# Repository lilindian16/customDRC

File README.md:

# Custom DRC for the Bit10 DSP

## Reverse Engineering

### Bit10 DRC Schema

## CustomDRC

### Bare PCB

### Assembled Board

Boards can be programmed via TC2030 header or 2.54mm pin header (left unpopulated). Once programmed,
further updates can be handled via the OTA Update interface through the local webapp

### Board Bringup - Scope Captures

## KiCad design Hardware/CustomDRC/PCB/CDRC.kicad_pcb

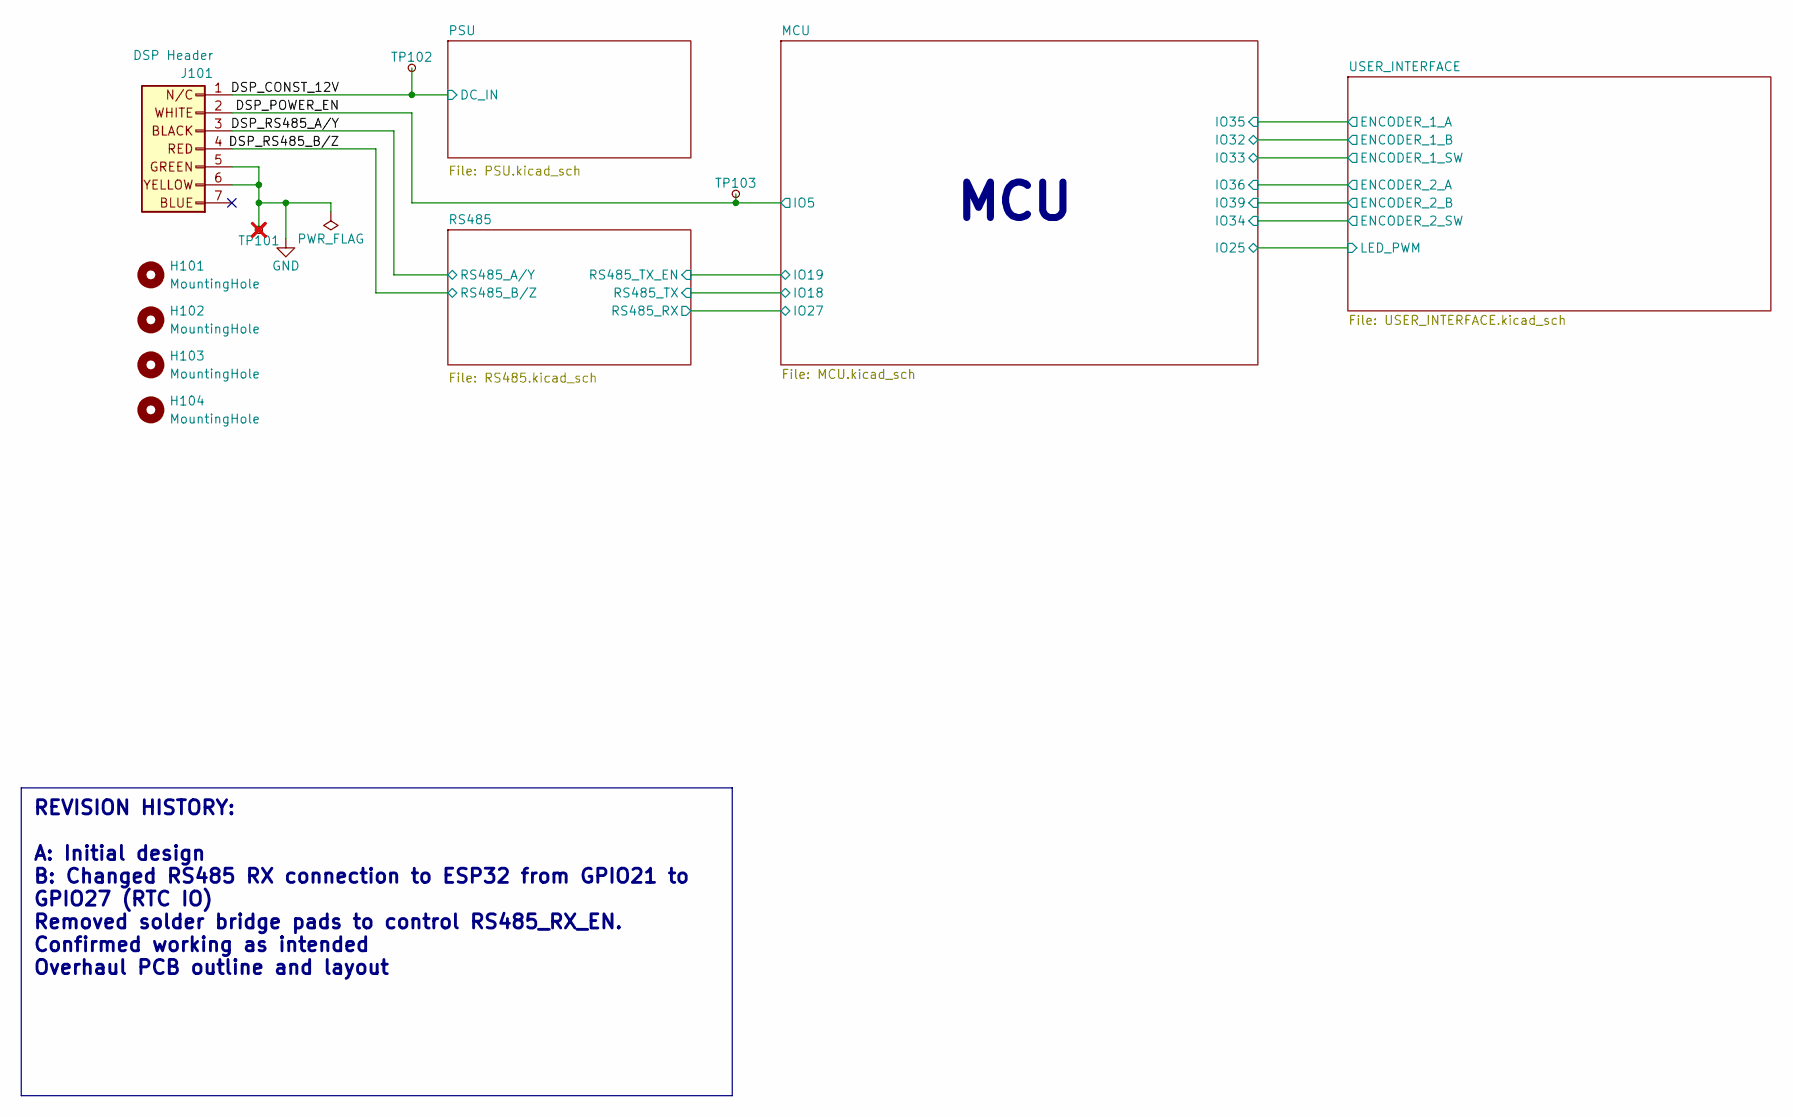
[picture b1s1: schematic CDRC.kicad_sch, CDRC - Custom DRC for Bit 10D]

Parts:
H101, H102, H103, H104: MountingHole; MountingHole_2.7mm_M2.5_ISO7380_Pad_TopBottom
J101: DSP Header; M208900705; MPN KH-2.54PH-1X30P-L13.5-WT; LCSC C20610239
TP101: TestPoint_Small; TestPoint_Keystone_5000-5004_Miniature; MPN RH-5001; LCSC C5199801; not fitted
TP102, TP103: TestPoint_Small; TestPoint_Pad_D1.5mm

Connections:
/DSP_CONST_12V: J101.1, TP102.1; also elsewhere on the board
/DSP_POWER_EN: J101.2, TP103.1; also elsewhere on the board
/DSP_RS485_A/Y: J101.3; also elsewhere on the board
/DSP_RS485_B/Z: J101.4; also elsewhere on the board
GND: J101.5, J101.6, TP101.1; also elsewhere on the board

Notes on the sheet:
REVISION HISTORY: A: Initial design B: Changed RS485 RX connection to ESP32 from GPIO21 to GPIO27 (RTC IO) Removed solder bridge pads to control RS485_RX_EN. Confirmed working as intended Overhaul PCB outline and layout
MCU

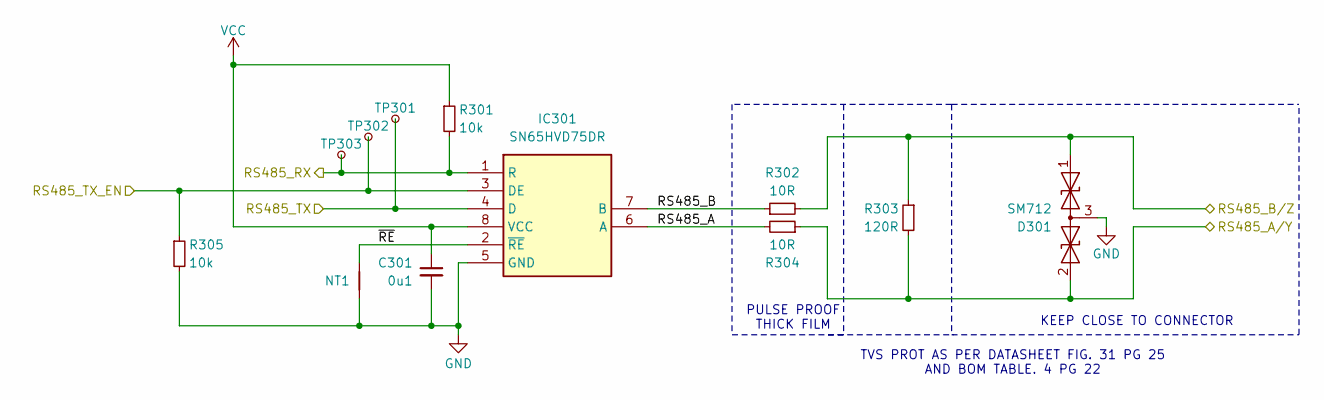
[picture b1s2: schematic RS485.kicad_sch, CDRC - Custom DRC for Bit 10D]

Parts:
C301: 0u1; C_0603_1608Metric_Pad1.08x0.95mm_HandSolder; MPN CC0603KRX7R9BB104; LCSC C14663
D301: SM712; SOT-23; MPN SM712; LCSC C5243888
IC301: SN65HVD75DR; SOIC-8_3.9x4.9mm_P1.27mm; Manufacturer_Part_Number SN65HVD75DR; Mouser Part Number 595-SN65HVD75DR
NT1: NetTie_2; NetTie-2_SMD_Pad0.5mm
R301, R305: 10k; R_0603_1608Metric_Pad0.98x0.95mm_HandSolder; MPN 0603WAF1002T5E; LCSC C25804
R302, R304: 10R; R_0603_1608Metric_Pad0.98x0.95mm_HandSolder; MPN CRCW060310R0FKTA; LCSC C2091419
R303: 120R; R_0603_1608Metric_Pad0.98x0.95mm_HandSolder; MPN 0603WAF1200T5E; LCSC C22787
TP301, TP302, TP303: TestPoint_Small; TestPoint_Pad_D1.5mm

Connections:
/DSP_RS485_A/Y: D301.2 (A2), R303.2, R304.1; also elsewhere on the board
/DSP_RS485_B/Z: D301.1 (A1), R302.2, R303.1; also elsewhere on the board
/MCU/IO18: IC301.4 (D), TP301.1; also elsewhere on the board
/MCU/IO19: IC301.3 (DE), R305.1, TP302.1; also elsewhere on the board
/MCU/IO27: IC301.1 (R), R301.2, TP303.1; also elsewhere on the board
/RS485/RS485_A: IC301.6 (A), R304.2
/RS485/RS485_B: IC301.7 (B), R302.1
/RS485/~RE: IC301.2 (~RE), NT1.2
GND: C301.2, D301.3 (common), IC301.5 (GND), NT1.1, R305.2; also elsewhere on the board
VCC: C301.1, IC301.8 (VCC), R301.1; also elsewhere on the board

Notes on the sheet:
KEEP CLOSE TO CONNECTOR
TVS PROT AS PER DATASHEET FIG. 31 PG 25 AND BOM TABLE. 4 PG 22
PULSE PROOF THICK FILM

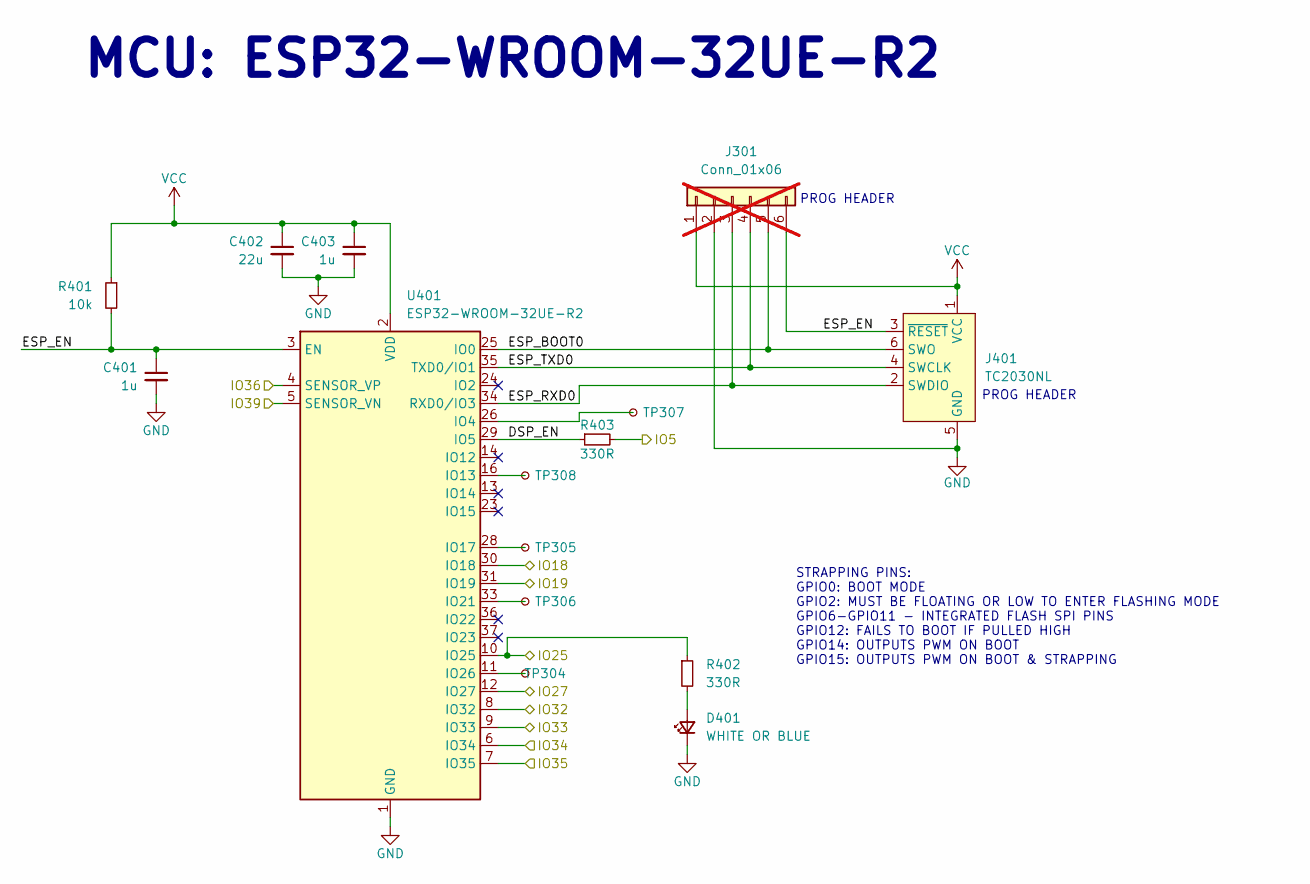
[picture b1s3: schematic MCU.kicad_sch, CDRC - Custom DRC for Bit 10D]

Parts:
C401, C403: 1u; C_0603_1608Metric_Pad1.08x0.95mm_HandSolder; MPN CL10A105KB8NNNC; LCSC C15849
C402: 22u; C_0805_2012Metric_Pad1.18x1.45mm_HandSolder; MPN CL21A226MAQNNNE; LCSC C45783
D401: WHITE OR BLUE; LED_0603_1608Metric_Pad1.05x0.95mm_HandSolder; MPN KT-0603W; LCSC C2290
J301: Conn_01x06; PinSocket_1x06_P2.54mm_Vertical; not fitted
J401: TC2030NL; Tag-Connect_TC2030-IDC-FP_2x03_P1.27mm_Vertical
R401: 10k; R_0603_1608Metric_Pad0.98x0.95mm_HandSolder; MPN 0603WAF1002T5E; LCSC C25804
R402, R403: 330R; R_0603_1608Metric_Pad0.98x0.95mm_HandSolder; MPN 0603WAF3300T5E; LCSC C23138
TP304, TP305, TP306, TP307, TP308: TestPoint_Small; TestPoint_Pad_D1.5mm
U401: ESP32-WROOM-32UE-R2; ESP32-WROOM-32UE; MPN ESP32-WROOM-32UE-N16; LCSC C701346

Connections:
/DSP_POWER_EN: R403.2; also elsewhere on the board
/MCU/DSP_EN: R403.1, U401.29 (IO5)
/MCU/ESP_BOOT0: J301.5, J401.6 (SWO), U401.25 (IO0)
/MCU/ESP_EN: C401.1, J301.6, J401.3 (~RESET), R401.2, U401.3 (EN)
/MCU/ESP_RXD0: J301.3, J401.2 (SWDIO), U401.34 (RXD0/IO3)
/MCU/ESP_TXD0: J301.4, J401.4 (SWCLK), U401.35 (TXD0/IO1)
/MCU/IO18: U401.30 (IO18); also elsewhere on the board
/MCU/IO19: U401.31 (IO19); also elsewhere on the board
/MCU/IO25: R402.1, U401.10 (IO25); also elsewhere on the board
/MCU/IO27: U401.12 (IO27); also elsewhere on the board
/MCU/IO32: U401.8 (IO32); also elsewhere on the board
/MCU/IO33: U401.9 (IO33); also elsewhere on the board
/MCU/IO34: U401.6 (IO34); also elsewhere on the board
/MCU/IO35: U401.7 (IO35); also elsewhere on the board
/MCU/IO36: U401.4 (SENSOR_VP); also elsewhere on the board
/MCU/IO39: U401.5 (SENSOR_VN); also elsewhere on the board
GND: C401.2, C402.2, C403.2, D401.1 (K), J301.2, J401.5 (GND), U401.1 (GND), U401.15 (GND), U401.38 (GND), U401.39 (GND); also elsewhere on the board
unnamed: D401.2 (A), R402.2
unnamed: TP307.1, U401.26 (IO4)
unnamed: TP308.1, U401.16 (IO13)
unnamed: TP305.1, U401.28 (IO17)
unnamed: TP306.1, U401.33 (IO21)
unnamed: TP304.1, U401.11 (IO26)
VCC: C402.1, C403.1, J301.1, J401.1 (VCC), R401.1, U401.2 (VDD); also elsewhere on the board

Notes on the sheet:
PROG HEADER
MCU: ESP32-WROOM-32UE-R2
STRAPPING PINS: GPIO0: BOOT MODE GPIO2: MUST BE FLOATING OR LOW TO ENTER FLASHING MODE GPIO6-GPIO11 - INTEGRATED FLASH SPI PINS GPIO12: FAILS TO BOOT IF PULLED HIGH GPIO14: OUTPUTS PWM ON BOOT GPIO15: OUTPUTS PWM ON BOOT & STRAPPING

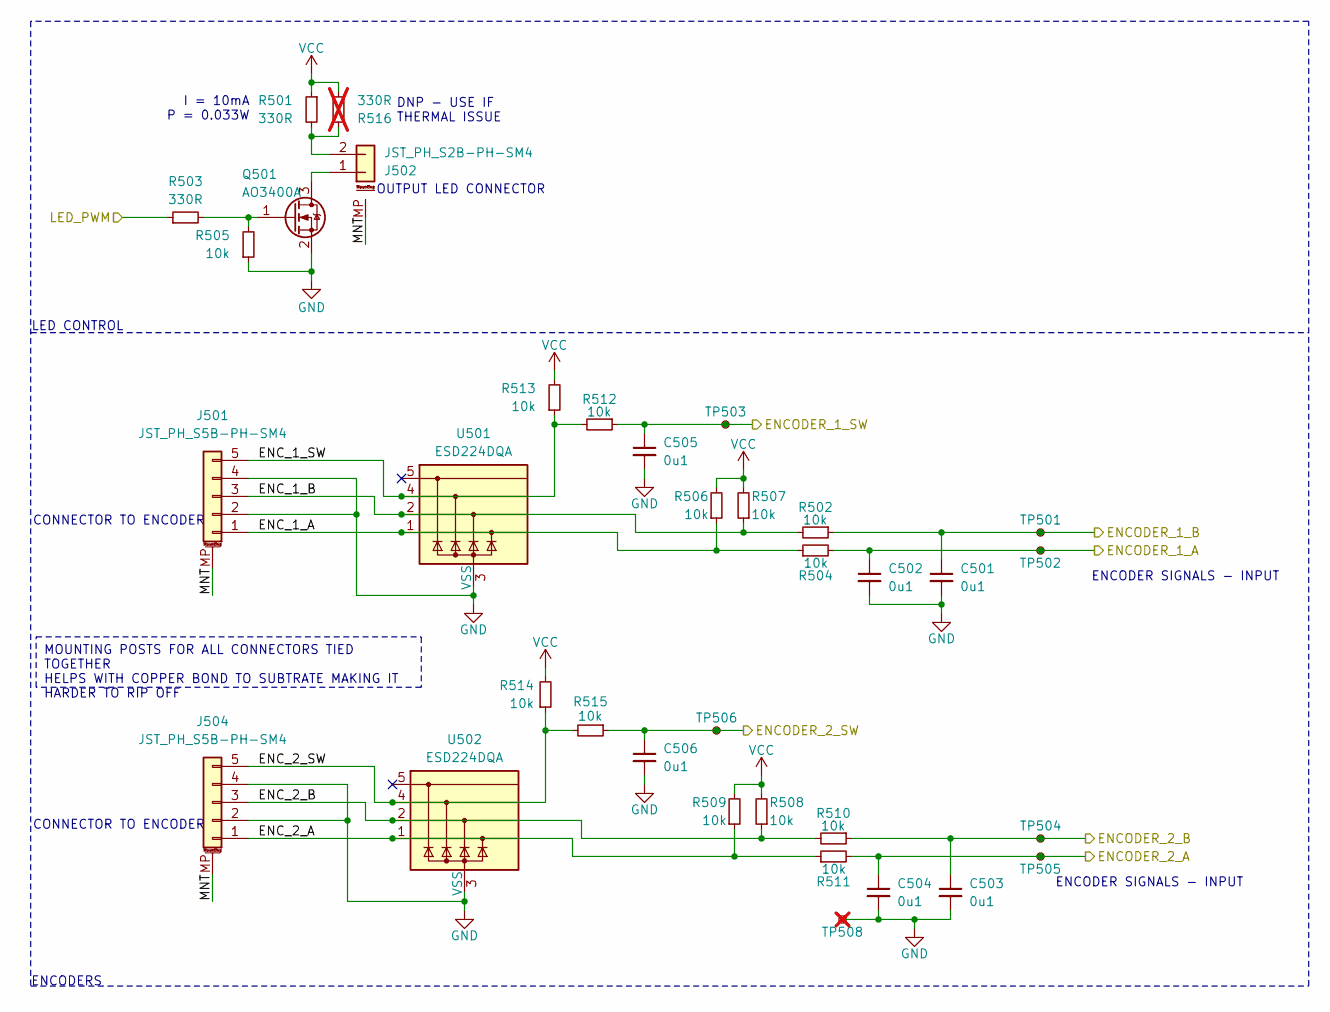
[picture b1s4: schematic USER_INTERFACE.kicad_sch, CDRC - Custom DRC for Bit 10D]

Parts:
C501, C502, C503, C504, C505, C506: 0u1; C_0603_1608Metric_Pad1.08x0.95mm_HandSolder; MPN CC0603KRX7R9BB104; LCSC C14663
J501, J504: JST_PH_S5B-PH-SM4; JST_PH_S5B-PH-SM4-TB_1x05-1MP_P2.00mm_Horizontal; MPN S5B-PH-SM4-TB(LF)(SN); LCSC C265104
J502: JST_PH_S2B-PH-SM4; JST_PH_S2B-PH-SM4-TB_1x02-1MP_P2.00mm_Horizontal; MPN S2B-PH-SM4-TB(LF)(SN); LCSC C295747
Q501: AO3400A; SOT-23; MPN AO3400A; LCSC C20917
R501, R503: 330R; R_0603_1608Metric_Pad0.98x0.95mm_HandSolder; MPN 0603WAF3300T5E; LCSC C23138
R502, R504, R505, R506, R507, R508, R509, R510, R511, R512, R513, R514, R515: 10k; R_0603_1608Metric_Pad0.98x0.95mm_HandSolder; MPN 0603WAF1002T5E; LCSC C25804
R516: 330R; R_1206_3216Metric_Pad1.30x1.75mm_HandSolder; MPN 1206W4J0331T5E; LCSC C25374; not fitted
TP501, TP502, TP503, TP504, TP505, TP506: TestPoint_Small; TestPoint_Pad_D1.5mm
TP508: TestPoint_Small; TestPoint_Keystone_5000-5004_Miniature; MPN RH-5001; LCSC C5199801; not fitted
U501, U502: ESD224DQA; Diodes_UDFN-10_1.0x2.5mm_P0.5mm; MPN RClAMP3324P-ES; LCSC C5199157

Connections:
/MCU/IO25: R503.1; also elsewhere on the board
/MCU/IO32: C501.1, R502.1, TP501.1; also elsewhere on the board
/MCU/IO33: C505.1, R512.1, TP503.1; also elsewhere on the board
/MCU/IO34: C506.1, R515.1, TP506.1; also elsewhere on the board
/MCU/IO35: C502.1, R504.2, TP502.1; also elsewhere on the board
/MCU/IO36: C504.1, R511.2, TP505.1; also elsewhere on the board
/MCU/IO39: C503.1, R510.1, TP504.1; also elsewhere on the board
/USER_INTERFACE/ENC_1_A: J501.1, R504.1, R506.1, U501.1, U501.10
/USER_INTERFACE/ENC_1_B: J501.3, R502.2, R507.1, U501.2, U501.9
/USER_INTERFACE/ENC_1_SW: J501.5, R512.2, R513.1, U501.4, U501.7
/USER_INTERFACE/ENC_2_A: J504.1, R509.1, R511.1, U502.1, U502.10
/USER_INTERFACE/ENC_2_B: J504.3, R508.1, R510.2, U502.2, U502.9
/USER_INTERFACE/ENC_2_SW: J504.5, R514.1, R515.2, U502.4, U502.7
/USER_INTERFACE/MNT: J501.MP (MountPin), J502.MP (MountPin), J504.MP (MountPin)
GND: C501.2, C502.2, C503.2, C504.2, C505.2, C506.2, J501.2, J501.4, J504.2, J504.4, Q501.2 (S), R505.1, TP508.1, U501.3 (VSS), U501.8 (VSS), U502.3 (VSS), U502.8 (VSS); also elsewhere on the board
unnamed: J502.1, Q501.3 (D)
unnamed: J502.2, R501.2, R516.1
unnamed: Q501.1 (G), R503.2, R505.2
VCC: R501.1, R506.2, R507.2, R508.2, R509.2, R513.2, R514.2, R516.2; also elsewhere on the board

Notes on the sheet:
MOUNTING POSTS FOR ALL CONNECTORS TIED TOGETHER HELPS WITH COPPER BOND TO SUBTRATE MAKING IT HARDER TO RIP OFF
ENCODER SIGNALS - INPUT
OUTPUT LED CONNECTOR
CONNECTOR TO ENCODER
LED CONTROL
I = 10mA P = 0.033W
ENCODERS
DNP - USE IF THERMAL ISSUE

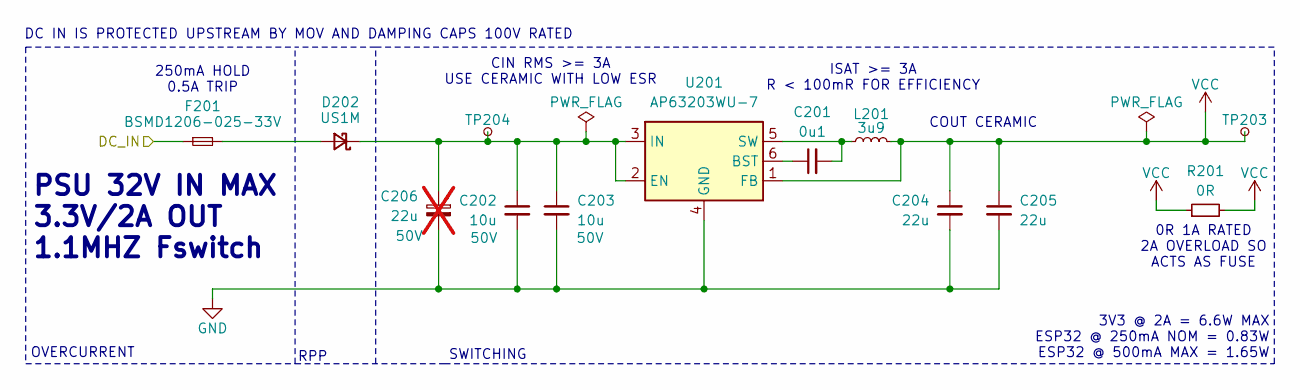
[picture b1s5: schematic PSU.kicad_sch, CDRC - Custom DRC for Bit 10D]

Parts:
C201: 0u1; C_0603_1608Metric_Pad1.08x0.95mm_HandSolder; MPN CC0603KRX7R9BB104; LCSC C14663
C202, C203: 10u; C_1206_3216Metric_Pad1.33x1.80mm_HandSolder; Voltage Rating 50V; MPN CL31B106KBHNNNE; LCSC C89632
C204, C205: 22u; C_0805_2012Metric_Pad1.18x1.45mm_HandSolder; MPN CL21A226MAQNNNE; LCSC C45783
C206: 22u; CP_Elec_6.3x5.4_Nichicon; Voltage Rating 50V; not fitted
D202: US1M; D_SMA_Handsoldering; MPN US1M; LCSC C412437
F201: BSMD1206-025-33V; Fuse_1206_3216Metric_Pad1.42x1.75mm_HandSolder; MPN BSMD1206-025-33V; LCSC C2977524
L201: 3u9; L_Cenker_CKCS4030; MPN SWPA4030S3R9MT; LCSC C96899
R201: 0R; R_0603_1608Metric_Pad0.98x0.95mm_HandSolder; MPN 0603WAF0000T5E; LCSC C21189
TP203, TP204: TestPoint_Small; TestPoint_Pad_D1.5mm
U201: AP63203WU-7; TSOT-23-6; MPN AP63203WU-7; LCSC C780769

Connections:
/DSP_CONST_12V: F201.1; also elsewhere on the board
GND: C202.2, C203.2, C204.2, C205.2, C206.2, U201.4 (GND); also elsewhere on the board
unnamed: D202.2 (A), F201.2
unnamed: C202.1, C203.1, C206.1, D202.1 (K), TP204.1, U201.2 (EN), U201.3 (IN)
unnamed: C201.1, U201.6 (BST)
unnamed: C201.2, L201.1, U201.5 (SW)
VCC: C204.1, C205.1, L201.2, R201.1, R201.2, TP203.1, U201.1 (FB); also elsewhere on the board

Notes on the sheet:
COUT CERAMIC
3V3 @ 2A = 6.6W MAX ESP32 @ 250mA NOM = 0.83W ESP32 @ 500mA MAX = 1.65W
OVERCURRENT
ISAT >= 3A R < 100mR FOR EFFICIENCY
DC IN IS PROTECTED UPSTREAM BY MOV AND DAMPING CAPS 100V RATED
RPP
0R 1A RATED 2A OVERLOAD SO ACTS AS FUSE
CIN RMS >= 3A USE CERAMIC WITH LOW ESR
PSU 32V IN MAX 3.3V/2A OUT 1.1MHZ Fswitch
250mA HOLD 0.5A TRIP
SWITCHING

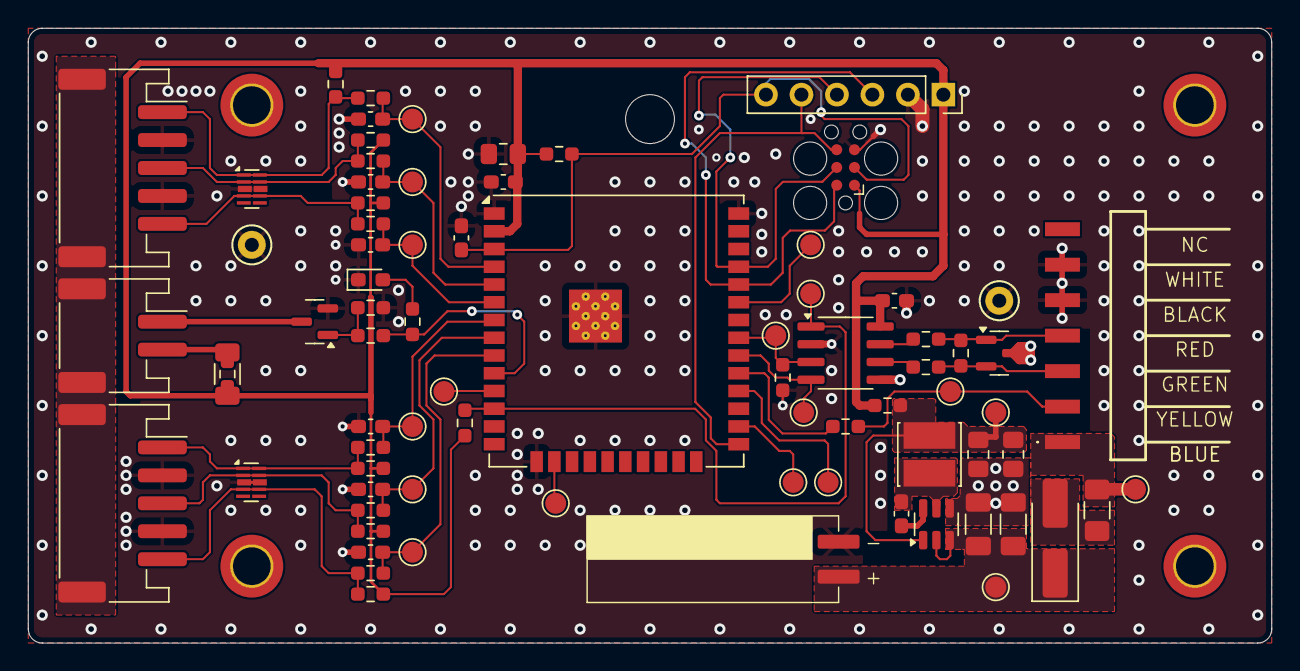
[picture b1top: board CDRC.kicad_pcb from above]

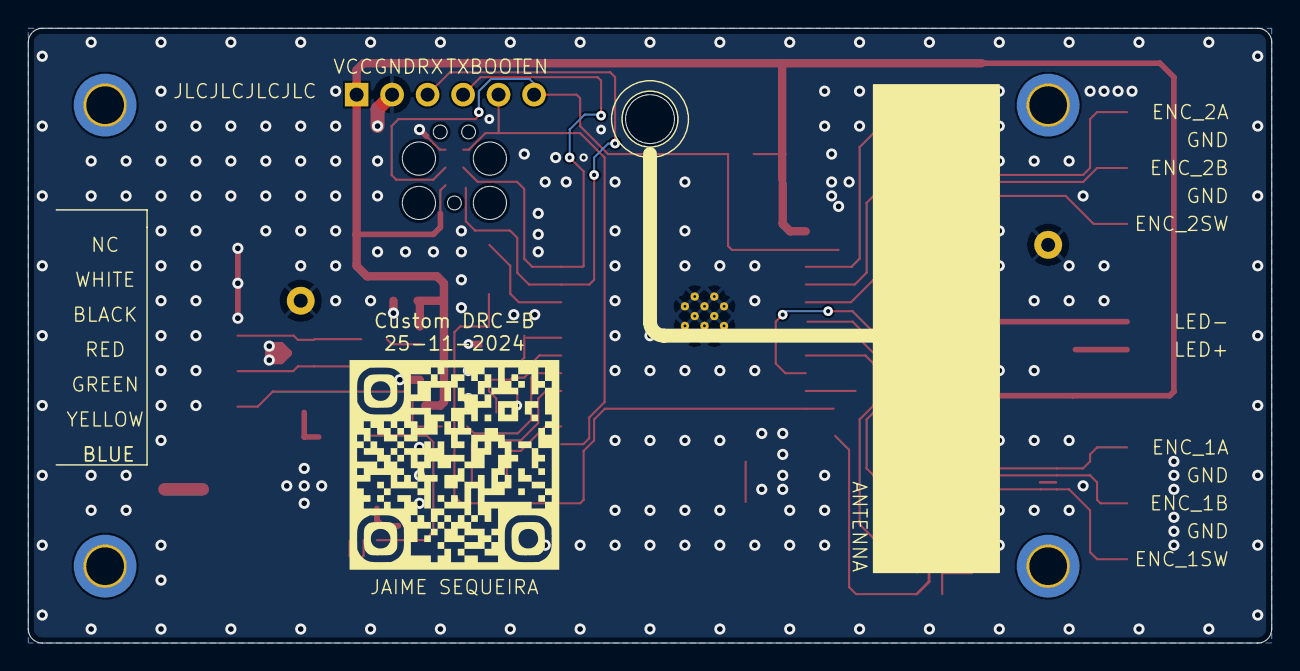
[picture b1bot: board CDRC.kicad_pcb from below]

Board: 2 copper layers, 89.0 x 44.0 mm, 83 parts (4 on the bottom side), 44 nets.

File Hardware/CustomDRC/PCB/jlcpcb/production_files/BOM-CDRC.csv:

Comment,Designator,Footprint,LCSC,Quantity
0u1,"C201,C301,C501,C502,C503,C504,C505,C506",C_0603_1608Metric_Pad1.08x0.95mm_HandSolder,C14663,8
1u,"C401,C403",C_0603_1608Metric_Pad1.08x0.95mm_HandSolder,C15849,2
100U,,Capacitor_D6.3xL12mm_SMD,C160200,0
DSP Header,J101,M208900705,C20610239,1
10R,"R302,R304",R_0603_1608Metric_Pad0.98x0.95mm_HandSolder,C2091419,2
AO3400A,Q501,SOT-23,C20917,1
0R,R201,R_0603_1608Metric_Pad0.98x0.95mm_HandSolder,C21189,1
120R,R303,R_0603_1608Metric_Pad0.98x0.95mm_HandSolder,C22787,1
WHITE OR BLUE,D401,LED_0603_1608Metric_Pad1.05x0.95mm_HandSolder,C2290,1
330R,"R402,R403,R501,R503",R_0603_1608Metric_Pad0.98x0.95mm_HandSolder,C23138,4
10k,"R301,R305,R401,R502,R504,R505,R506,R507,R508,R509,R510,R511,R512,R513,R514,R515",R_0603_1608Metric_Pad0.98x0.95mm_HandSolder,C25804,16
JST_PH_S5B-PH-SM4,"J501,J504",JST_PH_S5B-PH-SM4-TB_1x05-1MP_P2.00mm_Horizontal,C265104,2
JST_PH_S2B-PH-SM4,J502,JST_PH_S2B-PH-SM4-TB_1x02-1MP_P2.00mm_Horizontal,C295747,1
BSMD1206-025-33V,F201,Fuse_1206_3216Metric_Pad1.42x1.75mm_HandSolder,C2977524,1
US1M,D202,D_SMA_Handsoldering,C412437,1
22u,"C204,C205,C402",C_0805_2012Metric_Pad1.18x1.45mm_HandSolder,C45783,3
ESD224DQA,"U501,U502",Diodes_UDFN-10_1.0x2.5mm_P0.5mm,C5199157,2
SM712,D301,SOT-23,C5243888,1
SN65HVD75DR,IC301,SOIC-8_3.9x4.9mm_P1.27mm,C57928,1
ESP32-WROOM-32UE-R2,U401,ESP32-WROOM-32UE,C701346,1
AP63203WU-7,U201,TSOT-23-6,C780769,1
10u,"C202,C203",C_1206_3216Metric_Pad1.33x1.80mm_HandSolder,C89632,2
3u9,L201,L_Cenker_CKCS4030,C96899,1

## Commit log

2024-08-16 Added gitignore
2024-08-16 Project update
    Created the actual readme
2024-08-16 Update
    Start of firmware dev. First attempt at writing on the AC Link bus
2024-08-16 Update gitignore
2024-08-20 Started working on rx
2024-08-20 Remove 9BitUART source since we are rebasing to use ESP32 HW
2024-08-20 Scrap atmelavr for ESP32
2024-08-20 Change source file name to reflect what we actually use it for
2024-08-20 Add support for software serial source
2024-08-20 Update main source to remove use of AtmelAVR framwork
2024-08-20 Added link for RS485 packet capture google doc
2024-08-20 Fixed comment typo
2024-08-20 Updated class to store the configured GPIO settings in private
2024-08-20 Added screenshot of working volume control
2024-08-20 Update
    Start work on HW dev with schema capture
2024-08-20 Update - OScope
    Added OScope screenshots for volume adjust verification
2024-08-20 Update - Class function call
    Updated function call to change volume given new class function architecture
2024-08-20 Update - Class functions
    Updated class functions to discretise the public functions into what should actually be public
2024-08-27 Update - Schematics
    Added new reverse engineered schematic. Also updated main PCB folder structure
2024-08-27 Fix - updated the programming header. Header uses +5V not VDC as power input
2024-08-31 Update - Added schematic PDF to repo
2024-08-31 Update - Added JLC production folder and files
2024-08-31 Update - finished schematic for revision A
2024-08-31 Update - Added functions for volume control, fader, balance and subwoofer control
2024-08-31 Updated main source for latest AC Link lib updates
2024-08-31 Update - updated README with the HW report GDoc linK
2024-09-01 Update - Start of FE design for the controller
2024-09-01 Update - Upload Rev A PCB step model
2024-09-02 Start of web UI dev
2024-09-02 Working on DOM. Added default display values for range inputs
2024-09-02 Update todo list
2024-09-04 Added vscode workspace to gitignore
2024-09-04 Started work on webserver for ESP32
2024-09-04 Created a file parser to convert html/css/js to C header files
2024-09-04 Added pico minified to local dev
2024-09-04 Converted CDN to local file lookup for hosting with ESP32
2024-09-04 First html/css/js header file trials. Working well
2024-09-08 Update - Custom partitions
    Added custom partition defs for flash. Supports OTA and SPIFFS
2024-09-08 Changed custom DRC folder name
2024-09-08 Added TCP lib for Async support
2024-09-08 Added support for Async webserver
2024-09-08 Added ArduinoJson lib dependency
2024-09-08 Sync HW changes for V1 PCB
2024-09-08 Update - File conversion tool
    Created a tool to convert HTML/CSS/JS to header files for C
2024-09-08 Sync with latest FE work
2024-09-08 Sync latest FW work
2024-09-08 Fix - Changed step size of subVolume to 1 from 0.5
2024-09-08 Update - Added JSON key value functionality
    JSON is now parsed when websocket message is received. KV pair is calculated and evaluated as required
2024-09-08 Update - added password KV handling
2024-09-08 Sync latest FE header files
2024-09-08 Fix - Added quote marks for password entry JSON. Also added min and max values for all range inputs
2024-09-08 Update to latest FE
2024-09-10 Update FrontEndDesign folder name to WebDesign
2024-09-10 Added readme for dev
2024-09-10 Put screenshot at top of readme
2024-09-10 Created image dir for repo
2024-09-10 Updated hedaer folder name
2024-09-10 Updated output folder name
2024-09-10 Updated folder structure
2024-09-10 Removed HTML footer. Since we run a local webserver, the links cannot point anywhere
2024-09-10 Added screenshot of PCB to readme
2024-09-10 Added screenshots of PCB and enclosure
2024-09-10 Update readme with screenshots of web interface scale on different devices
2024-09-10 Added captions to readme images
2024-09-10 Added project summary description
2024-09-11 Update - partition table updated for OTA handling
2024-09-11 Update - OTA
    Added full support for OTA update via the webserver interface
2024-09-11 Update - OTA
    Added OTA update support. We not check which partition is running on boot. Will need a better firmware version handling system
2024-09-11 Added support for OTA file upload and update trigger
2024-09-13 Created blinky to test HW spinup
2024-09-13 Created board env varibales for PIO
2024-09-13 Created case STL files
2024-09-13 Added HTML BOM for assembly
2024-09-13 Updated value of L201 from 4u7 to 3u9
2024-09-16 Change - Changed lib folder to CustomDRC and included all source files into it
2024-09-16 Update - incldue encoder lib
2024-09-16 Updated lib structure
2024-09-16 Update - started working on encoder integration. Volume encoder working for now
2024-09-16 Added encoder and SMPSU oscope captures
2024-09-16 Added encoder src files
2024-09-17 Fixed typo in readme
2024-09-17 Updated src structure and naming. Added support for triggering link bus activity on webpage events through websockets
2024-09-18 Update server functions to support sending control data through websocket
2024-09-18 Update to support updating data through websockets
2024-09-22 Removed password entry page. The softAP already has password auth
2024-10-27 Updated custom partitions to use recommended 8M by espressif
2024-10-27 Removed extra env for default esp32
2024-10-27 Added NVS lib
2024-10-27 Removed unnecessary board config file
2024-10-27 Refactored main to only call init function. Loop is idle
2024-10-27 Added bus connection display. Also added temp footer with FW version. Will need to be dynamically updated by FW
2024-10-27 Added support for all messages from DRC to be parsed by web server and display to update
2024-10-27 Added funcs to enable and disable encoders
2024-10-27 Added custom_drc src as main point of entry for program
2024-10-27 Major changes to AC_Link src. We now support most commands on bus and have everything up and running in TX and RX tasks
2024-10-27 Webserver supports updating the FE through websockets with much simpler implementation - parameter and value func. Value needs to be updated to pointer with length as third param
2024-10-27 Sync latest FE builds
2024-10-27 Reformat source with clang-format file for auto formatting
2024-10-27 Update naming of address enum. The main MCU in the DSP is address 0x00. The DSP processor is 0x46 and the computer on USB is 0x5A
2024-10-27 Changed name and label for third input to Digital Optical
2024-10-27 Changed wording for disabled RS485 bus
2024-10-30 Added cycle to wait and check when both master MCU and DSP processor are on the bus before giving them the current settings
2024-10-30 Updated commands and functions to support latest dev
2024-10-30 Added function to update a webserver parameter with a string input
2024-10-30 BREAKING CHANGE UPDATE! Changed pin assignment for RS485 RX. We had to route to a test-pad to allow the device to wakeup from activity on the bus. GPIO_NUM_27 operates in the VDD_RTC power domain so 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
2024-10-30 Fix: fixed state machine for controlling when encoders are active (USB is not connected). Also fixed the enabling mechanism to update the encoder with the latest count as it can update through USB se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
2024-10-30 Added on_button_clicked declaration
2024-10-30 Changed inputSource HTML element to be a string. We now support this and can update using the parameter update string function
2024-10-30 Added input source as an NVS parameter
2024-10-30 Added timeout for the RX task. If no device is on the bus after the allocated time, we shut down the DRC
2024-10-30 Added comments to header
2024-10-30 Removed MUTE functionality from the web server
2024-10-30 Added LED control via function and mode typedef
2024-10-30 Removed MUTE functionality from the web interface. Updated the source selection to match the workflow of the DRC->DSP
2024-11-01 Sync before making breaking changes to RS485 comms protocl and method
2024-11-02 RMT TX 9-bit serial transfer working (one at a time for now)
2024-11-02 UPDATE: Change RS485 TX to use RMT peripheral on ESP32. Offload transmission to hardware to reduce overhead when using softwareserial lib
2024-11-02 Fix: Added function call when memorySelect button is clicked
2024-11-02 Updated encoder task stack size
2024-11-02 Added delay before shutting down DRC
2024-11-04 Created a USB connected task. This task monitors the RS485 bus when USB is connected acting as a slave and parsing received messages
2024-11-04 Made message parse function public
2024-11-04 Fix: Give tx semaphore before parsing to avoid entering loop while waiting for semaphore
2024-11-04 Updated LED modes to include mode for USB CONNECTED event
2024-11-05 Ring buffer for TX items on bus fully implemented and working
2024-11-11 Improved performance of packet -> rmt item conversion. Removed conditional in for loop
2024-11-11 Optimised conversion of byte to item by removing conditional and using boolean in bit-shift instead
2024-11-11 Sync before removing ring buffer implementation
2024-11-11 Removed intermediary ring buffer system to reduce latency between user input and bus transmission
2024-11-15 Added comments to source
2024-11-15 Sync changes to Rev B HW
2024-11-15 Added untracked folders
2024-11-15 Removed unused trial source
2024-11-15 Remove brand name from readme
2024-11-19 Added board renders and PDF plots
2024-11-19 Update readme with Rev A updates
2024-11-19 Fixed incorrect url for images
2025-01-01 Update images folder with latest photos
2025-01-01 Updated readme with Rev B writeup
2025-01-01 Update HW folder with latest work on rev B
2025-01-01 Work completed on latest webpage design
2025-01-01 Update with latest build
2025-01-01 Fixed typo
2025-01-05 Created task to periodically handle user-input from the webserver. This mitigates a user inundating the inputs and causing havoc on the bus
2025-01-12 Fix: Corrected function call to control fader via web range slider
2025-01-12 Sync latest work
2025-01-16 Created build dir for release FW
2025-01-16 Changed behaviour for encoder switch press to change the DSP memory
2025-01-16 Fix - set the encoder values when using the webserver range element. This avoids the encoder starting at a different value than what is set by the range input
2025-01-16 Added function to set the current value of the encoders using their index
2025-01-16 Added support for updating build number automatically through PIO
2025-01-16 Update - support fully automated build version numbering system through PIO scripts
2025-01-16 Support automated build number
2025-01-16 Added pre build script for automated version control
2025-01-16 Created release FW
2025-01-16 Sync
2025-01-17 Fix - Update the web server when the memory is changed on button press
2025-06-17 A fresh start for branch
2025-06-17 Recursively removed dirs that were meant to be ignored by .gitignore
2025-12-12 Repo restructure - this repo is now only for HW
2025-12-12 Updated readme for repo
